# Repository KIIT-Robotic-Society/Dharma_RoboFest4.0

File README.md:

# DHARMA BOT :dog2::robot:

Dharma Bot is a sophisticated quadruped robotic dog featuring 12 degrees of freedom (DOF) for dynamic motion. The system includes a custom-designed remote control and smartwatch, which collectively offer seamless user interaction, control, and monitoring capabilities.

## Authors :writing_hand:

- [@mr-spaw](https://github.com/mr-spaw) :space_invader: [Electronics]
- [@LordCretivo](https://github.com/LordCretivo) :teddy_bear: [CAD Modelling]
- [@DeepseaBandit](https://github.com/DeepseaBandit) :smirk_cat: [Remote GUI & Hand Gripper]

## Documentation :notebook_with_decorative_cover:

[Documentation](https://docs.google.com/document/d/14A3U6bSW9qBQt6sxEBGoiQTC8-wSntHT5azrs7TC3jw/edit?usp=sharing)

## System Overview :joystick: 
Dharma Bot is composed of three primary, electronically independent subsystems:
1. **The Bot**: The robotic dog, with core control and motion capabilities.
2. **Smart Remote**: The main control interface for the bot, featuring a Raspberry Pi, touchscreen, and long-range communication.
3. **Smartwatch**: A peripheral control and monitoring device equipped with sensors and ESP-32-based communications.
4. **Turret System**: The turret system is a rotating module mounted on the bot, designed to carry cameras and sensors. It provides 360-degree horizontal rotation and adjustable vertical tilt, enabling the bot to monitor or track targets in multiple directions.
4. **Gripper**:  It also consist of a hand gripper which is a versatile, precision-handling tool with adjustable grip strength and articulated fingers. It enables the dog to pick up, hold, and manipulate objects, performing tasks like delivering items or interacting with its environment.

## Subsystems

### [Smart Watch](Utility_Watch/watch.md) :watch:
The smartwatch incorporates:
- **ESP-32 WROOM microcontroller**:The SoC of the embedded hardware.
- **OLED screen**: Displays real-time status, bot location, connectivity, and enemy detection data.
- **Pulse-meter sensor** and **GPS**: For monitoring the wearer's health and position.
- **Geotagging**: Logs location of deployed tags for tracking.
- **Heartbeat Monitoring**: In "Military Mode," it locks if the wearer’s pulse reads zero for over 30 seconds.
- **FailSafe Mechanism**: Notifies the remote of the current location upon triggering specific emergency conditions.
- **ESP-NOW Communication**: Provides secure data exchange between the smartwatch and the smart remote.

### [Smart Remote](Utility_Remote/remote.md)  :video_game:
Serving as the primary control hub, the smart remote includes:
- **Raspberry Pi and 7-inch HDMI Touchscreen**: For intuitive control of the whole system architecture.
- **LoRa and ESP-NOW Modules**: Enabling long-range communication up to 10 km in LoRA and about five meters of communication with ESP-NOW protocol
- **GeoTag Integration**: Displays tagged locations on a map for rescue and tracking.
- **Video Streaming**: ESP-32 S3 CAM streaming for real-time surveillance.
- **Manual Controls**: Joysticks, potentiometers, and switches for bot locomotion and firing systems.
- **GUI**: The remote’s GUI interface provides a user-friendly experience, offering control over various modes, video feeds, and sensor data

### [PoC Bot](main_BOT/PoC_Bot.md) :dog2:
The main bot integrates:
- **Teensy 4.1 Microcontroller**: Manages core functions, including servo control and scheduling of Tasks
- **ESP 32 S3 Development Board**: Controlling the Peripheral Electronics like GPS, ToF Sensors and Gyroscopic Readngs.
- **MG99R Servo Motors**: 12 servo motors for precise locomotion.
- **ESP-32 S3 Camera System**: A esp camera system for live video feed.
- **LIDAR and GPS Modules**: For navigation and environmental awareness.
- **Communication**:  Local esp aceess network and long-range LoRa for data exchange between subsystems.

### [ProtoType Bot](main_BOT/PoC_Bot.md) :guide_dog:
The main bot integrates the following components:

- **STM32H755ZI-Q**: Manages core functions, handles communication with the SBCs, and controls peripheral electronics and FOC drivers.
- **STM32G431KB**: Oversees data collection and analysis from the three IMUs.
- **STM32F446RE**: Manages the TOF sensor and facilitates communication through LORA and IBUS.
- **STM32G431-ESC1**: FOC driver with magnetic encoder, enabling precise position control of the BLDC motor.
- **CAN Bus**: All microcontrollers communicate via CAN Bus for synchronized control and data exchange.

### [Turret System](Turret_System/turret.md) :gun:
The turrent has:
- **Raspberry Pi**: Runs a local ML image recognition model and manages peripheral hardware.
- **ESP 32**: Controls the Servo motors

### [Hand Gripper](Gripper/Gripper.md) :mechanical_arm:
The gripper system features:

- **NVIDIA Jetson Orin Nano**: This powerful local SBC runs the reinforcement learning (RL) model, enabling real-time object recognition and environmental analysis using LIDAR and 3D cameras for seamless operation.
- **Waveshare Encoder Servo**: The encoder servo ensures precise and accurate movement of the gripper, allowing for fine-tuned control in handling objects.

## Project Context :star: :india:
This project was developed as part of RoboFest, held in 2024, organised by Gujarat Council on Science and Technology(GUJCOST).

The project has participated in the Grand Final of RoboFest Gujarat 4.0, hosted by the Gujarat Government, in Ahmedabad.

*Project Under Development*

## Social Media :star2:
[Website](https://krs.kiit.ac.in)
[Instagram](https://www.instagram.com/kiit_robotics.society?utm_source=ig_web_button_share_sheet&igsh=ZDNlZDc0MzIxNw==)
[Linkedin](https://www.linkedin.com/company/kiit-robotics-society-bbsr/mycompany/)

## Project Link :link:
https://github.com/KIIT-Robotic-Society/Dharma_RoboFest4.0.git

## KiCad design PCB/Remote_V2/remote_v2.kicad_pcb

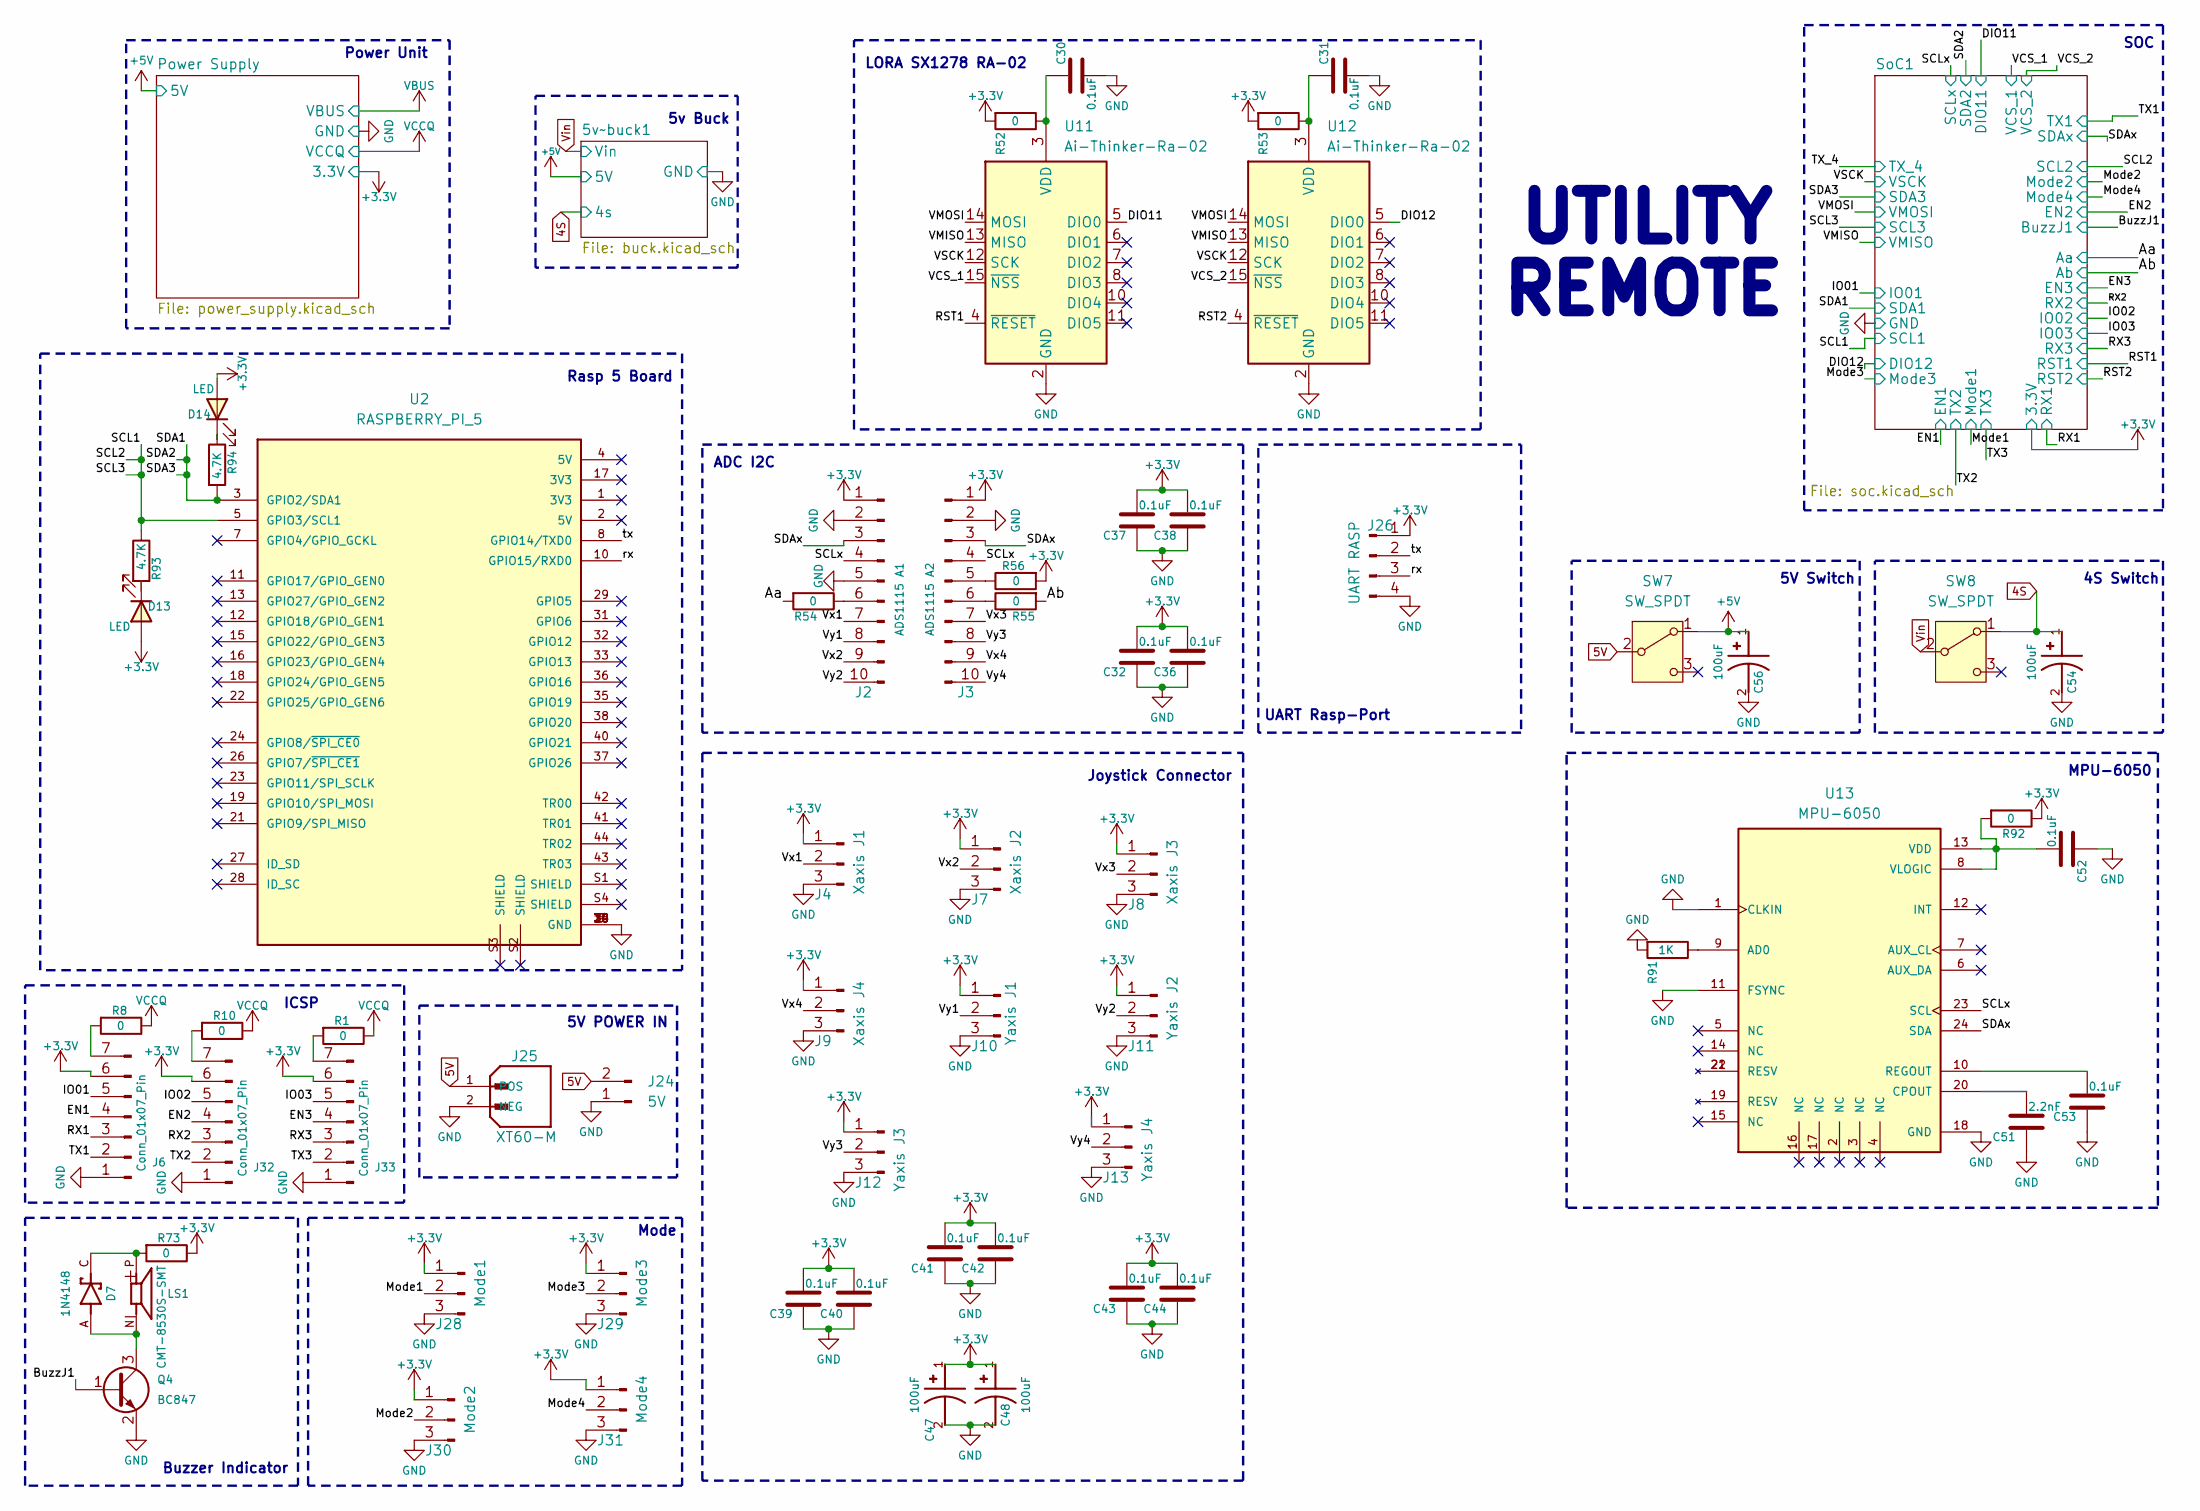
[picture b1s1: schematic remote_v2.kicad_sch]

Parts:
C30, C31, C32, C36, C37, C38, C39, C40, C41, C42, C43, C44, C52, C53: 0.1uF; C_0402_1005Metric
C47, C48, C54, C56: 100uF; CAPAE830X1000N; PARTREV CAT.8100L
C51: 2.2nF; C_0402_1005Metric
D7: 1N4148; D_SOD-323; PARTREV 31 Aug 2016
D13, D14: LED; LED_0402_1005Metric
J2: ADS1115 A1; PinHeader_1x10_P2.54mm_Vertical
J3: ADS1115 A2; PinHeader_1x10_P2.54mm_Vertical
J4: Xaxis J1; smd_pad_10
J6, J32, J33: Conn_01x07_Pin; solder_7
J7: Xaxis J2; smd_pad_10
J8: Xaxis J3; smd_pad_10
J9: Xaxis J4; smd_pad_10
J10: Yaxis J1; smd_pad_10
J11: Yaxis J2; smd_pad_10
J12: Yaxis J3; smd_pad_10
J13: Yaxis J4; smd_pad_10
J24: 5V; solder_motor
J25: XT60-M; AMASS_XT60PW-M; PARTREV V1.2
J26: UART RASP; solder_pad_4
J28: Mode1; smd_pad_10
J29: Mode3; smd_pad_10
J30: Mode2; smd_pad_10
J31: Mode4; smd_pad_10
LS1: CMT-8530S-SMT; CUI_CMT-8530S-SMT
Q4: BC847; SOT-23
R1, R8, R10, R52, R53, R54, R55, R56, R73, R92: 0; R_0402_1005Metric
R91: 1K; R_0402_1005Metric
R93, R94: 4.7K; R_0402_1005Metric
SW7, SW8: SW_SPDT; SW_Slide_1P2T_CK_OS102011MS2Q
U2: RASPBERRY_PI_5; MODULE_RASPBERRY_PI_4B_4GB; PARTREV 4
U11, U12: Ai-Thinker-Ra-02; Ai-Thinker-Ra-01-LoRa
U13: MPU-6050; QFN-24-1EP_3x3mm_P0.4mm_EP1.75x1.6mm; PARTREV 3.4

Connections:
4S: C54.1, SW8.1 (A); also elsewhere on the board
5V: J24.2, J25.1 (POS), SW7.2 (B)
+3.3V: C32.1, C36.1, C37.1, C38.1, C39.1, C40.1, C41.1, C42.1, C43.1, C44.1, C47.1, C48.1, D13.2 (A), D14.2 (A), J2.1, J3.1, J4.1, J6.6, J7.1, J8.1, J9.1, J10.1, J11.1, J12.1, J13.1, J26.1, J28.1, J29.1, J30.1, J31.1, J32.6, J33.6, R52.2, R53.2, R56.2, R73.1, R92.1; also elsewhere on the board
+5V: C56.1, SW7.1 (A); also elsewhere on the board
/Aa: R54.2; also elsewhere on the board
/Ab: R55.2; also elsewhere on the board
/BuzzJ1: Q4.1 (B); also elsewhere on the board
/DIO11: U11.5 (DIO0); also elsewhere on the board
/DIO12: U12.5 (DIO0); also elsewhere on the board
/EN1: J6.4; also elsewhere on the board
/EN2: J32.4; also elsewhere on the board
/EN3: J33.4; also elsewhere on the board
/IO01: J6.5; also elsewhere on the board
/IO02: J32.5; also elsewhere on the board
/IO03: J33.5; also elsewhere on the board
/Mode1: J28.2; also elsewhere on the board
/Mode2: J30.2; also elsewhere on the board
/Mode3: J29.2; also elsewhere on the board
/Mode4: J31.2; also elsewhere on the board
/RST1: U11.4 (~RESET); also elsewhere on the board
/RST2: U12.4 (~RESET); also elsewhere on the board
/RX1: J6.3; also elsewhere on the board
/RX2: J32.3; also elsewhere on the board
/RX3: J33.3; also elsewhere on the board
/SCL1: R93.1, U2.5 (GPIO3/SCL1); also elsewhere on the board
/SCLx: J2.4, J3.4, U13.23 (SCL); also elsewhere on the board
/SDA1: R94.2, U2.3 (GPIO2/SDA1); also elsewhere on the board
/SDAx: J2.3, J3.3, U13.24 (SDA); also elsewhere on the board
/TX1: J6.2; also elsewhere on the board
/TX2: J32.2; also elsewhere on the board
/TX3: J33.2; also elsewhere on the board
/VCS_1: U11.15 (~NSS); also elsewhere on the board
/VCS_2: U12.15 (~NSS); also elsewhere on the board
/VMISO: U11.13 (MISO), U12.13 (MISO); also elsewhere on the board
/VMOSI: U11.14 (MOSI), U12.14 (MOSI); also elsewhere on the board
/VSCK: U11.12 (SCK), U12.12 (SCK); also elsewhere on the board
/Vx1: J2.7, J4.2
/Vx2: J2.9, J7.2
/Vx3: J3.7, J8.2
/Vx4: J3.9, J9.2
/Vy1: J2.8, J10.2
/Vy2: J2.10, J11.2
/Vy3: J3.8, J12.2
/Vy4: J3.10, J13.2
/rx: J26.3, U2.10 (GPIO15/RXD0)
/tx: J26.2, U2.8 (GPIO14/TXD0)
GND: C30.1, C31.1, C32.2, C36.2, C37.2, C38.2, C39.2, C40.2, C41.2, C42.2, C43.2, C44.2, C47.2, C48.2, C51.2, C52.2, C53.2, C54.2, C56.2, J2.2, J2.5, J3.2, J4.3, J6.1, J7.3, J8.3, J9.3, J10.3, J11.3, J12.3, J13.3, J24.1, J25.2 (NEG), J26.4, J28.3, J29.3, J30.3, J31.3, J32.1, J33.1, Q4.2 (E), R91.2, U2.6 (GND), U2.9 (GND), U2.14 (GND), U2.20 (GND), U2.25 (GND), U2.30 (GND), U2.34 (GND), U2.39 (GND), U11.1 (GND), U11.2 (GND), U11.9 (GND), U11.16 (GND), U12.1 (GND), U12.2 (GND), U12.9 (GND), U12.16 (GND), U13.1 (CLKIN), U13.11 (FSYNC), U13.18 (GND); also elsewhere on the board
unnamed: D7.C, LS1.P, R73.2
unnamed: D13.1 (K), R93.2
unnamed: D14.1 (K), R94.1
unnamed: J2.6, R54.1
unnamed: J3.5, R56.1
unnamed: J3.6, R55.1
unnamed: J6.7, R8.2
unnamed: J32.7, R10.2
unnamed: J33.7, R1.2
unnamed: D7.A, LS1.N, Q4.3 (C)
unnamed: C30.2, R52.1, U11.3 (VDD)
unnamed: C31.2, R53.1, U12.3 (VDD)
unnamed: R91.1, U13.9 (AD0)
unnamed: C51.1, U13.20 (CPOUT)
unnamed: C53.1, U13.10 (REGOUT)
unnamed: C52.1, R92.2, U13.8 (VLOGIC), U13.13 (VDD)
VCCQ: R1.1, R8.1, R10.1; also elsewhere on the board
Vin: SW8.2 (B); also elsewhere on the board

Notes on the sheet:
UTILITY
Joystick Connector
Rasp 5 Board
Power Unit
LORA SX1278 RA-02
MPU-6050
5V Switch
ICSP
5V POWER IN
REMOTE
4S Switch
SOC
Mode
UART Rasp-Port
5v Buck
Buzzer Indicator
ADC I2C

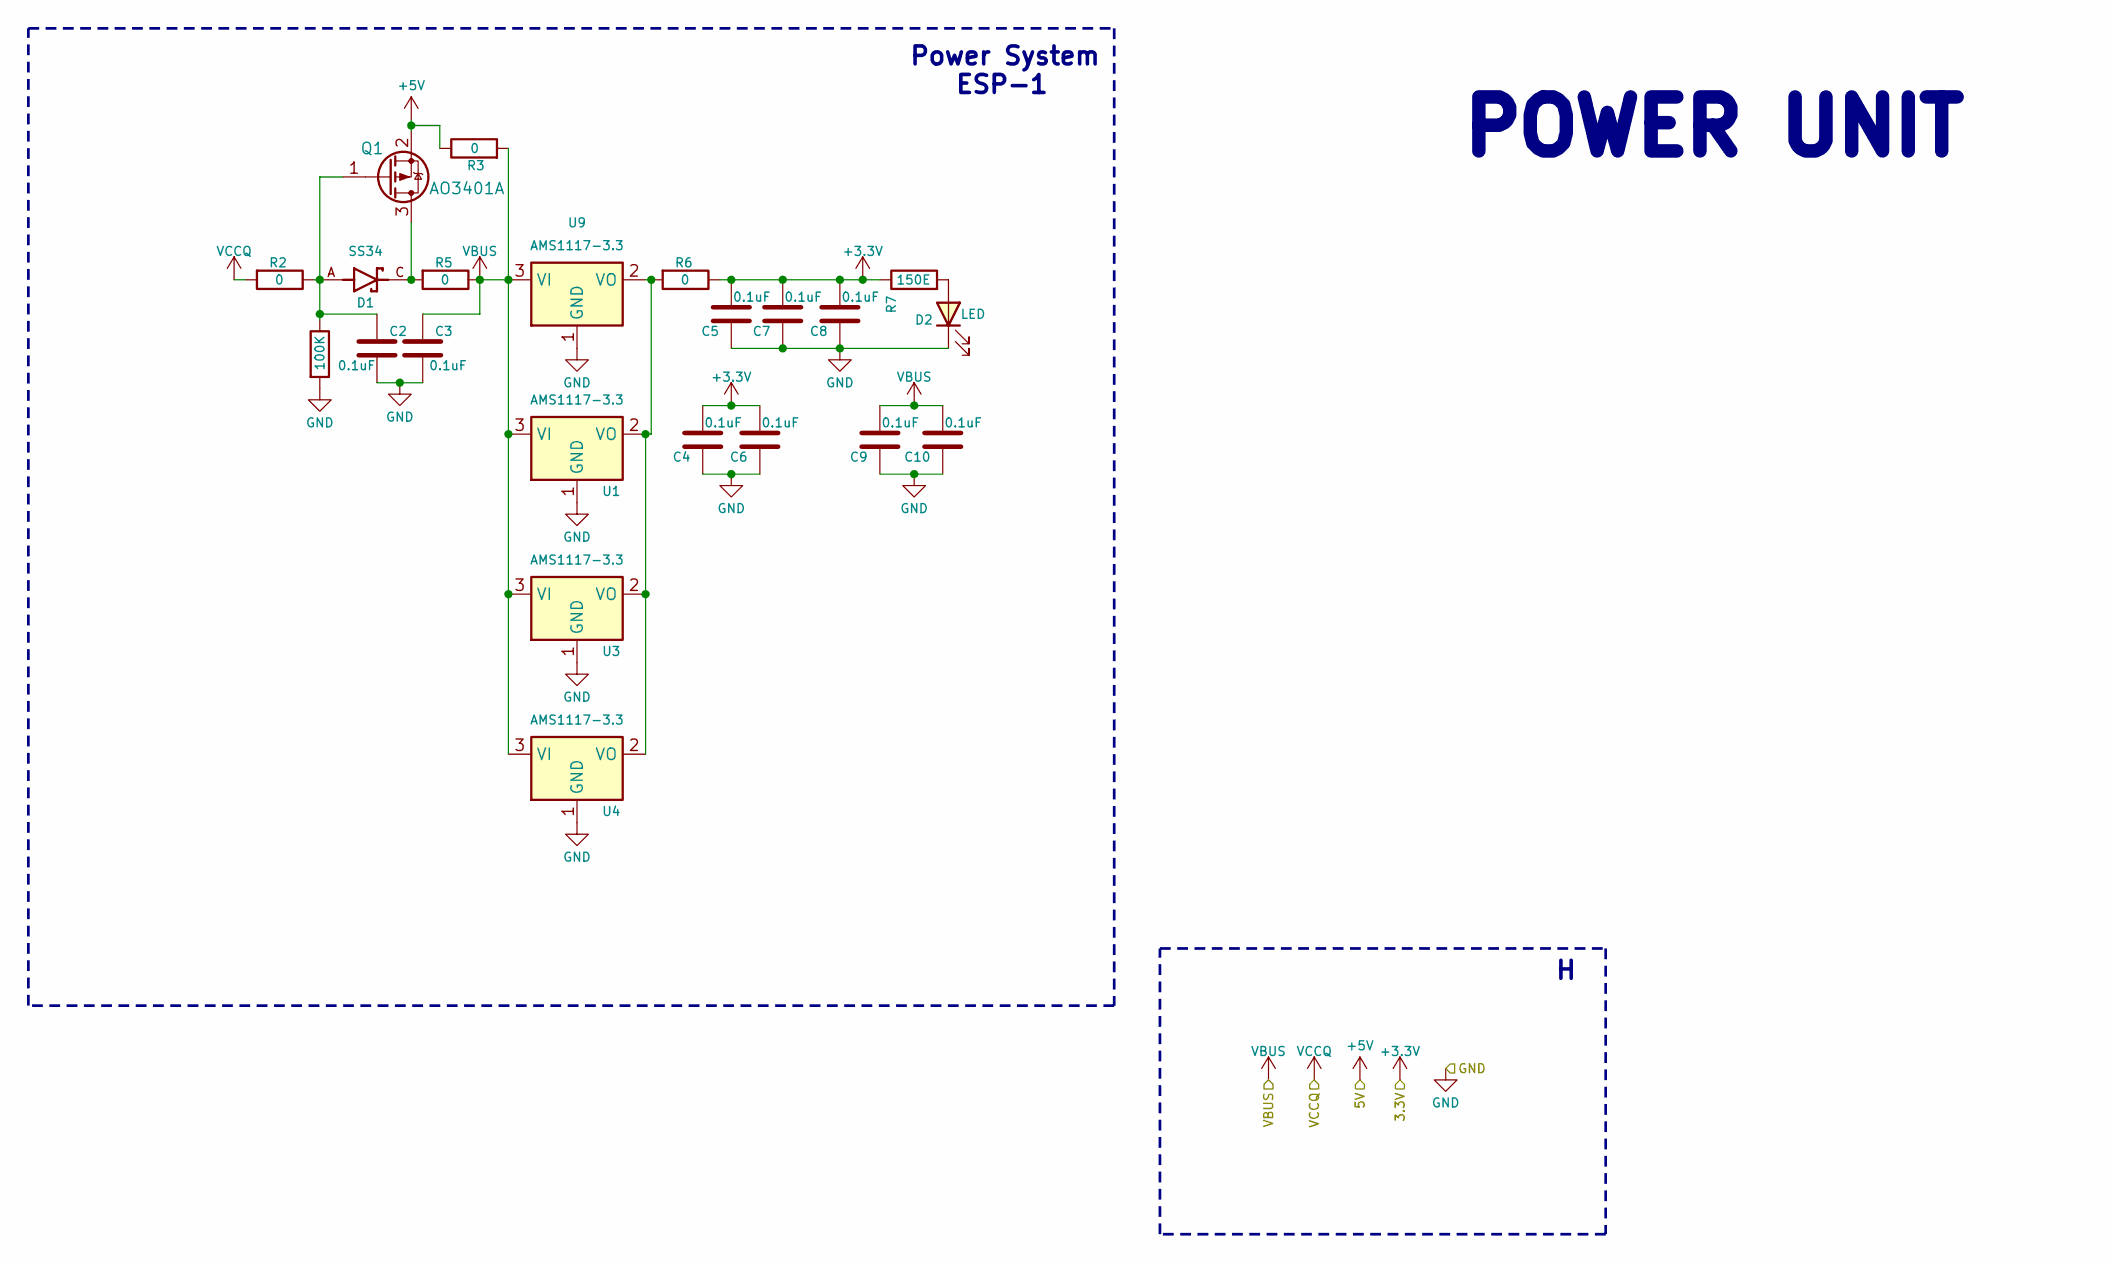
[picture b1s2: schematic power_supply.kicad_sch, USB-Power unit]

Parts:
C2, C3, C4, C5, C6, C7, C8, C9, C10: 0.1uF; C_0402_1005Metric
D1: SS34; P25_DO-214AC_SMA; PARTREV 31 Aug 2016
D2: LED; LED_0402_1005Metric
Q1: AO3401A; SOT-23
R2, R3, R5, R6: 0; R_0402_1005Metric
R4: 100K; R_0402_1005Metric
R7: 150E; R_0402_1005Metric
U1, U3, U4, U9: AMS1117-3.3; SOT-223-3_TabPin2

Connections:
+3.3V: C4.1, C5.1, C6.1, C7.1, C8.1, R6.1, R7.1; also elsewhere on the board
+5V: Q1.2 (S), R3.1; also elsewhere on the board
GND: C2.1, C3.1, C4.2, C5.2, C6.2, C7.2, C8.2, C9.2, C10.2, D2.1 (K), R4.2, U1.1 (GND), U3.1 (GND), U4.1 (GND), U9.1 (GND); also elsewhere on the board
unnamed: D2.2 (A), R7.2
unnamed: D1.C, Q1.3 (D), R5.2
unnamed: C2.2, D1.A, Q1.1 (G), R2.1, R4.1
unnamed: R6.2, U1.2 (VO), U3.2 (VO), U4.2 (VO), U9.2 (VO)
VBUS: C3.2, C9.1, C10.1, R3.2, R5.1, U1.3 (VI), U3.3 (VI), U4.3 (VI), U9.3 (VI)
VCCQ: R2.2; also elsewhere on the board

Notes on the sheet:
POWER UNIT
ESP-1
Power System

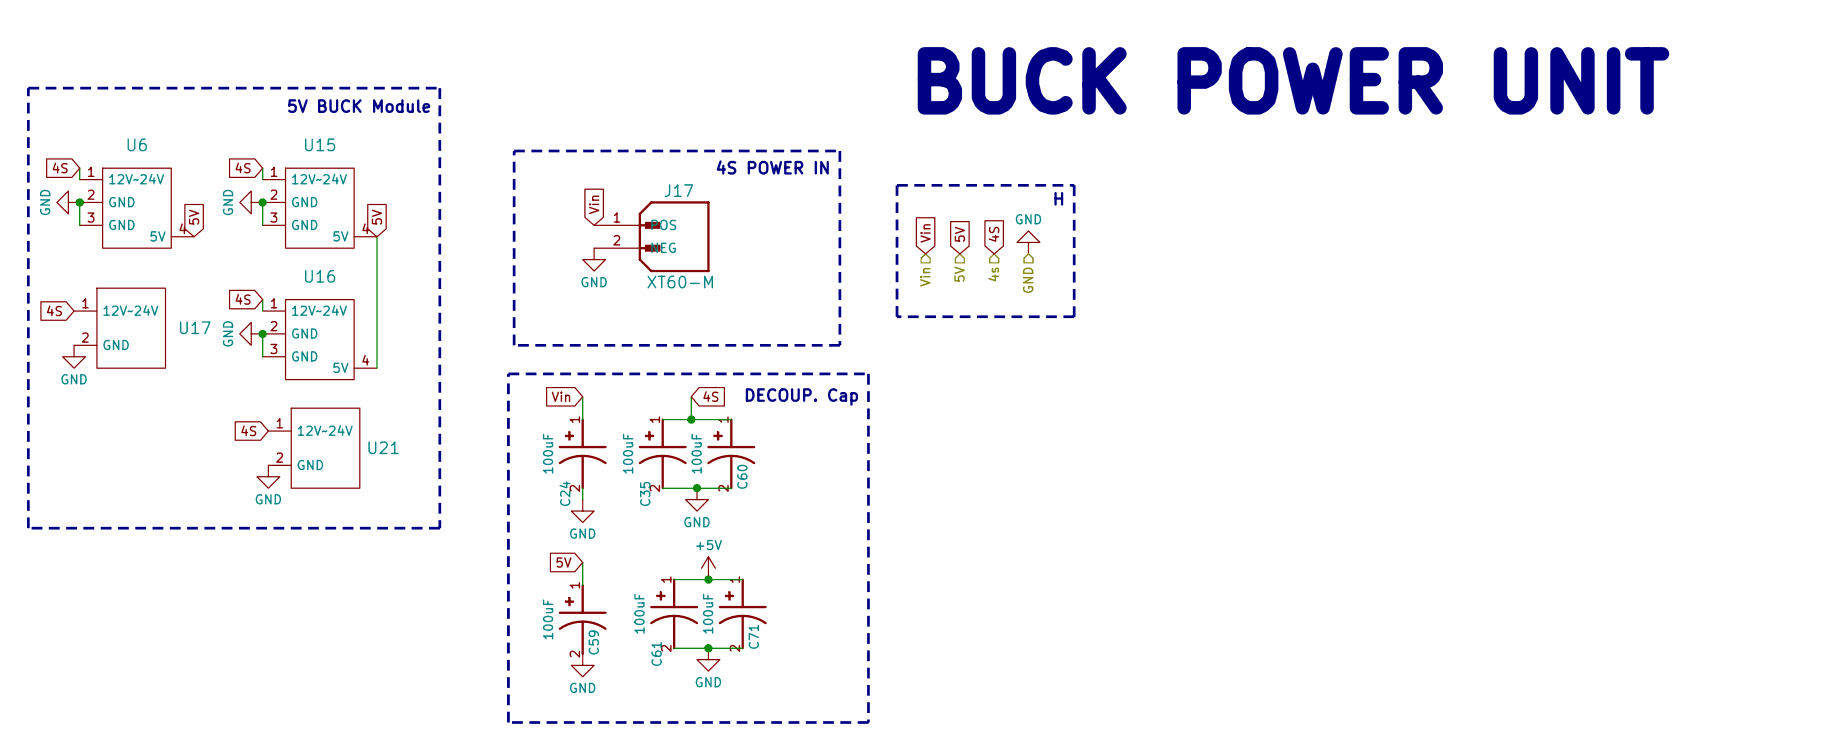
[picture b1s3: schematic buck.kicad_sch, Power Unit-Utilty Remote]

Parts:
C24, C35, C59, C60, C61, C71: 100uF; CAPAE830X1000N; PARTREV CAT.8100L
J17: XT60-M; AMASS_XT60PW-M; PARTREV V1.2
U6, U15, U16: buck 5v
U17, U21: 5v_usbbuck

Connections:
4S: C35.1, C60.1, U6.1 (12V~24V), U15.1 (12V~24V), U16.1 (12V~24V), U17.1 (12V~24V), U21.1 (12V~24V); also elsewhere on the board
+5V: C59.1, C61.1, C71.1, U6.4 (5V), U15.4 (5V), U16.4 (5V); also elsewhere on the board
GND: C24.2, C35.2, C59.2, C60.2, C61.2, C71.2, J17.2 (NEG), U6.2 (GND), U6.3 (GND), U15.2 (GND), U15.3 (GND), U16.2 (GND), U16.3 (GND), U17.2 (GND), U21.2 (GND); also elsewhere on the board
Vin: C24.1, J17.1 (POS); also elsewhere on the board

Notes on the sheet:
4S POWER IN
BUCK POWER UNIT
5V BUCK Module
DECOUP. Cap

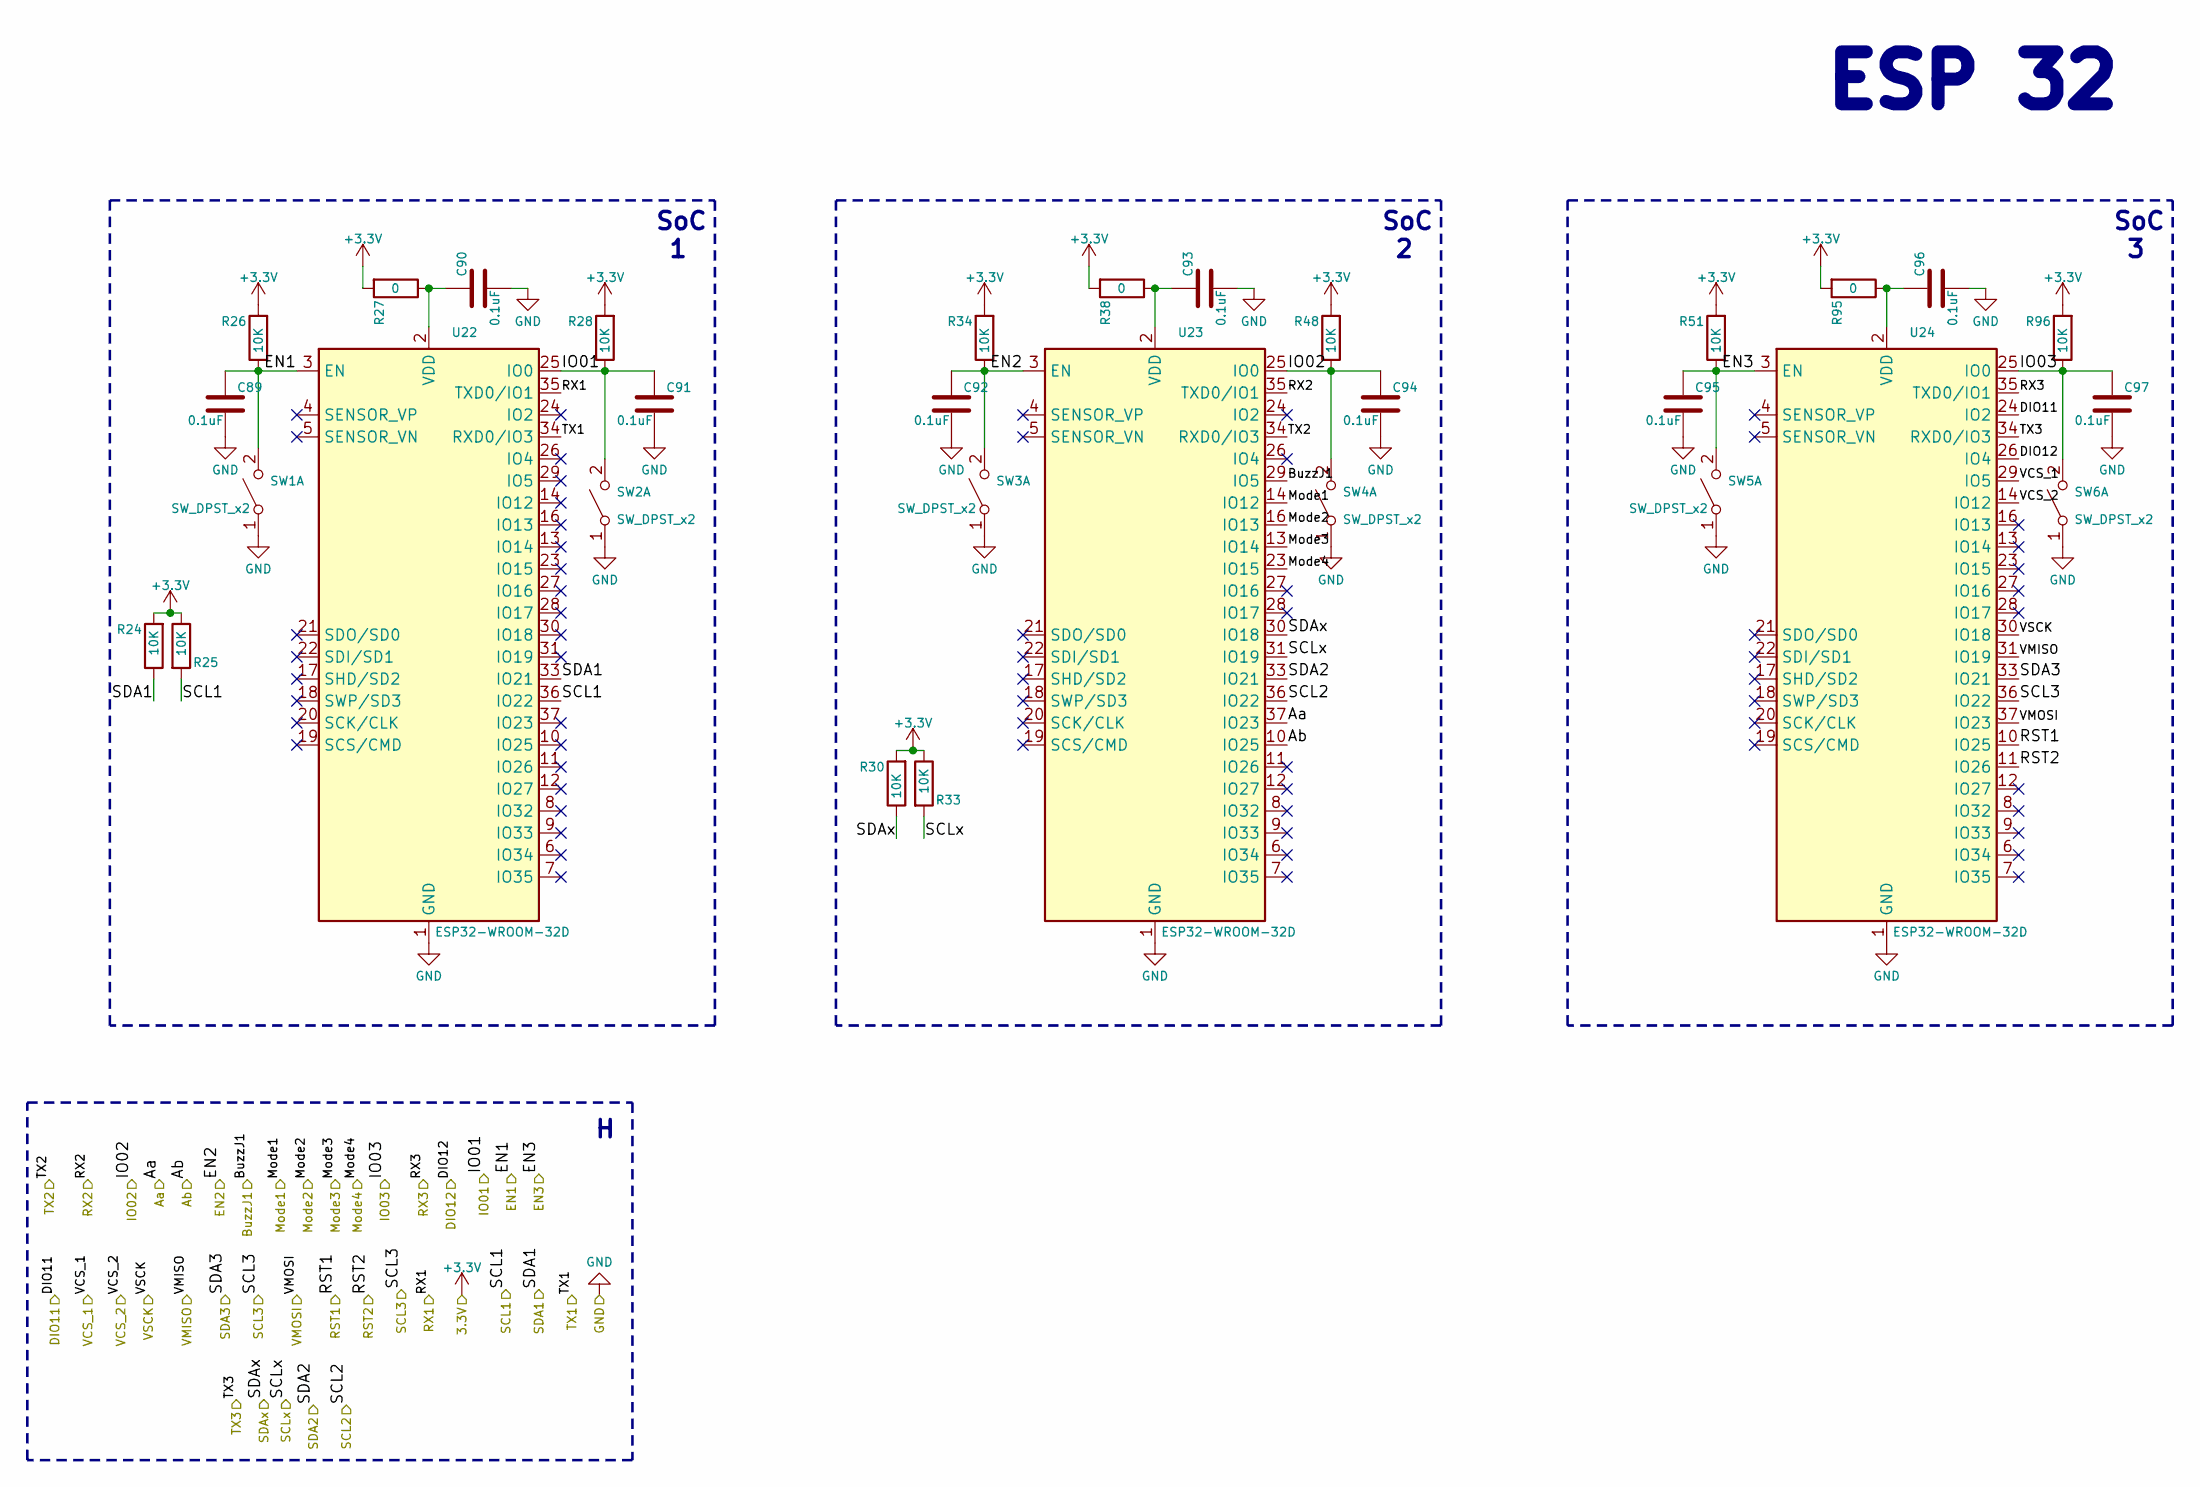
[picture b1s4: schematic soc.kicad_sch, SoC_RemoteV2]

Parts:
C89, C90, C91, C92, C93, C94, C95, C96, C97: 0.1uF; C_0402_1005Metric
R24, R25, R26, R28, R30, R33, R34, R48, R51, R96: 10K; R_0402_1005Metric
R27, R38, R95: 0; R_0402_1005Metric
SW1, SW2, SW3, SW4, SW5, SW6: SW_DPST_x2; SW_SPST_B3U-1000P-B
U22, U23, U24: ESP32-WROOM-32D

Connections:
+3.3V: R24.2, R25.1, R26.2, R27.2, R28.2, R30.2, R33.1, R34.2, R38.2, R48.2, R51.2, R95.2, R96.2; also elsewhere on the board
/Aa: U23.37 (IO23); also elsewhere on the board
/Ab: U23.10 (IO25); also elsewhere on the board
/BuzzJ1: U23.29 (IO5); also elsewhere on the board
/DIO11: U24.24 (IO2); also elsewhere on the board
/DIO12: U24.26 (IO4); also elsewhere on the board
/EN1: C89.2, R26.1, SW1.2 (B), U22.3 (EN); also elsewhere on the board
/EN2: C92.2, R34.1, SW3.2 (B), U23.3 (EN); also elsewhere on the board
/EN3: C95.2, R51.1, SW5.2 (B), U24.3 (EN); also elsewhere on the board
/IO01: C91.2, R28.1, SW2.2 (B), U22.25 (IO0); also elsewhere on the board
/IO02: C94.2, R48.1, SW4.2 (B), U23.25 (IO0); also elsewhere on the board
/IO03: C97.2, R96.1, SW6.2 (B), U24.25 (IO0); also elsewhere on the board
/Mode1: U23.14 (IO12); also elsewhere on the board
/Mode2: U23.16 (IO13); also elsewhere on the board
/Mode3: U23.13 (IO14); also elsewhere on the board
/Mode4: U23.23 (IO15); also elsewhere on the board
/RST1: U24.10 (IO25); also elsewhere on the board
/RST2: U24.11 (IO26); also elsewhere on the board
/RX1: U22.35 (TXD0/IO1); also elsewhere on the board
/RX2: U23.35 (TXD0/IO1); also elsewhere on the board
/RX3: U24.35 (TXD0/IO1); also elsewhere on the board
/SCL1: R25.2, U22.36 (IO22), U23.36 (IO22), U24.36 (IO22); also elsewhere on the board
/SCLx: R33.2, U23.31 (IO19); also elsewhere on the board
/SDA1: R24.1, U22.33 (IO21), U23.33 (IO21), U24.33 (IO21); also elsewhere on the board
/SDAx: R30.1, U23.30 (IO18); also elsewhere on the board
/TX1: U22.34 (RXD0/IO3); also elsewhere on the board
/TX2: U23.34 (RXD0/IO3); also elsewhere on the board
/TX3: U24.34 (RXD0/IO3); also elsewhere on the board
/VCS_1: U24.29 (IO5); also elsewhere on the board
/VCS_2: U24.14 (IO12); also elsewhere on the board
/VMISO: U24.31 (IO19); also elsewhere on the board
/VMOSI: U24.37 (IO23); also elsewhere on the board
/VSCK: U24.30 (IO18); also elsewhere on the board
GND: C89.1, C90.1, C91.1, C92.1, C93.1, C94.1, C95.1, C96.1, C97.1, SW1.1 (A), SW2.1 (A), SW3.1 (A), SW4.1 (A), SW5.1 (A), SW6.1 (A), U22.1 (GND), U22.15 (GND), U22.38 (GND), U22.39 (GND), U23.1 (GND), U23.15 (GND), U23.38 (GND), U23.39 (GND), U24.1 (GND), U24.15 (GND), U24.38 (GND), U24.39 (GND); also elsewhere on the board
unnamed: C90.2, R27.1, U22.2 (VDD)
unnamed: C93.2, R38.1, U23.2 (VDD)
unnamed: C96.2, R95.1, U24.2 (VDD)

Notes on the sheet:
SoC 1
ESP 32
SoC 2
SoC 3

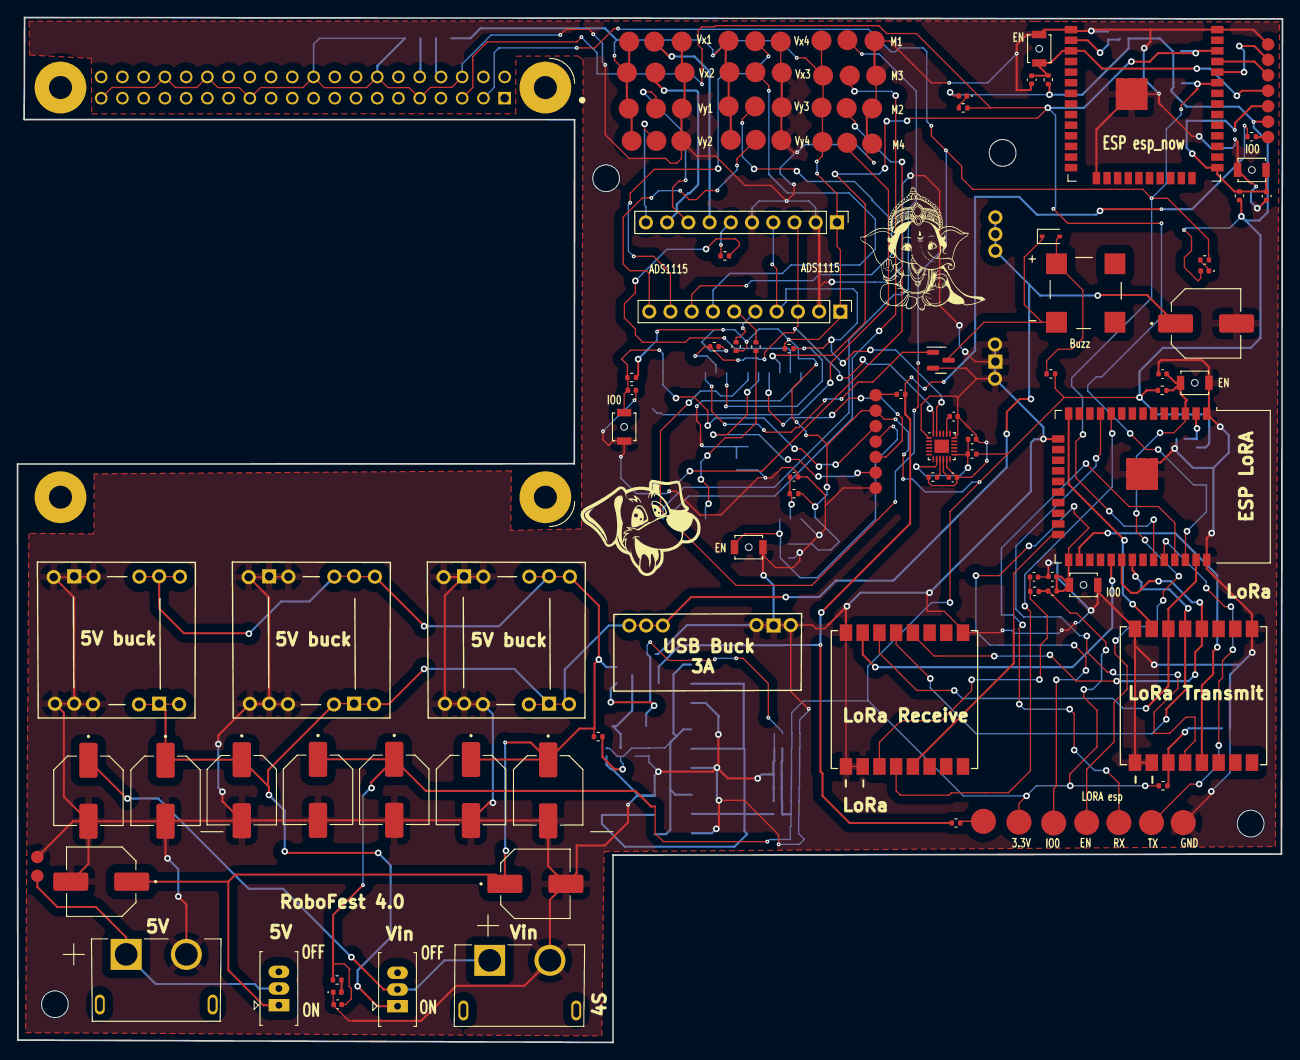
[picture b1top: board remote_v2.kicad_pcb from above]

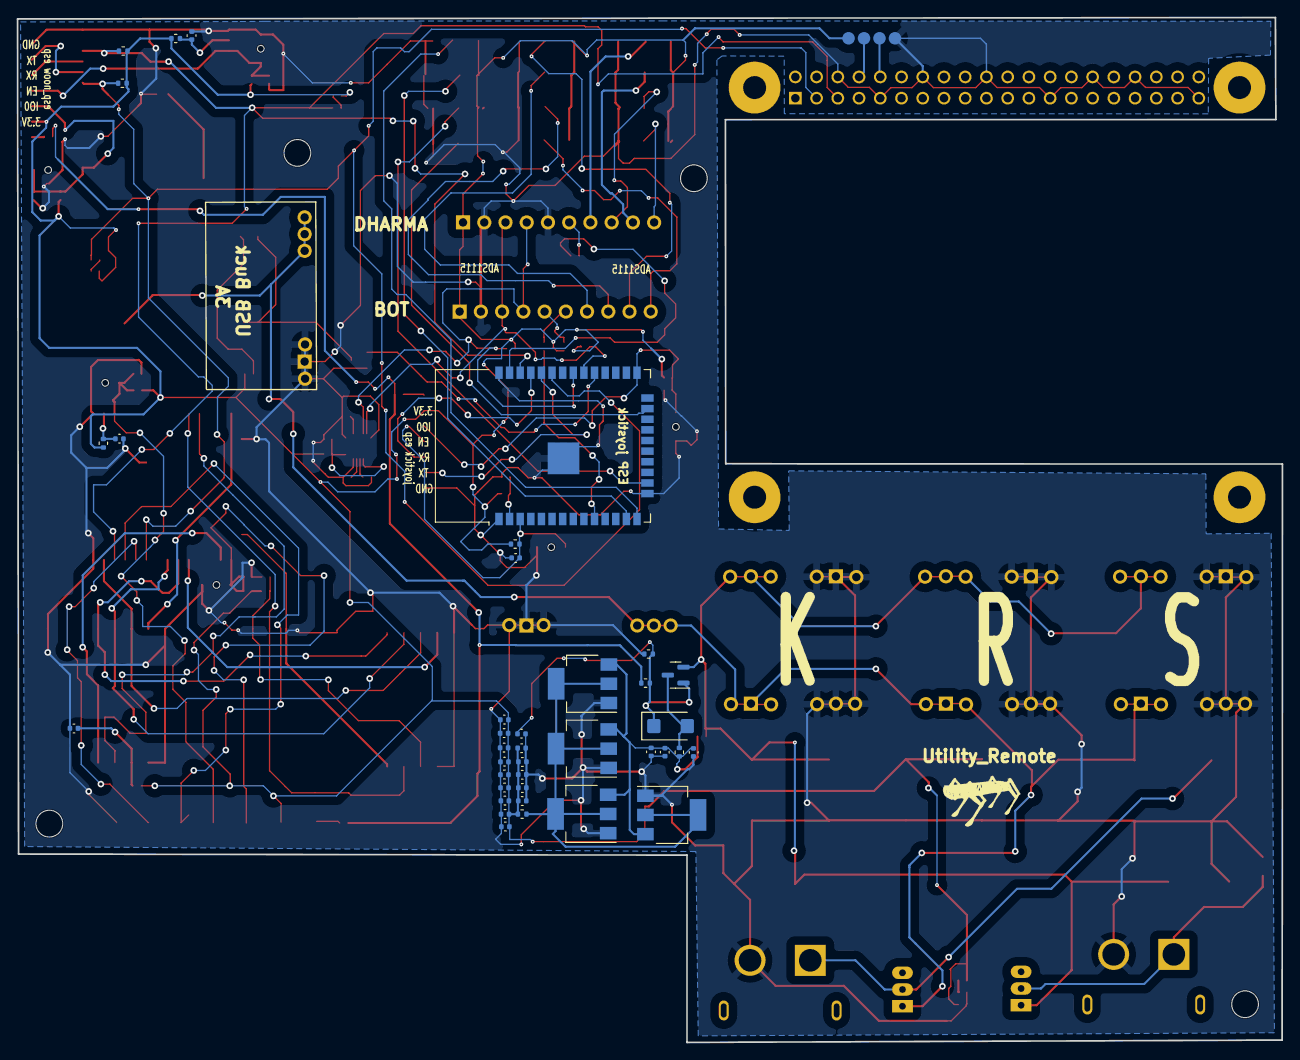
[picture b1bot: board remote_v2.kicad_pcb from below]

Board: 2 copper layers, 151.3 x 122.6 mm, 128 parts (40 on the bottom side), 73 nets.
